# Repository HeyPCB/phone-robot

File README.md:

# Bolt, the phone stand robot

**A little robot that holds your phone, charges it, and peeks over the top to tell you how it's eating.**

Bolt is a matte-black robot phone stand with gold eyes. Two kickstands snap out of its belly and slot through its hips; they become the hands your phone sits on, in landscape, leaning back at 70 degrees. Your charger plugs into its left foot and your phone's cable into its right: a 5 V USB-C pass-through that powers the phone port only when a phone is attached, offers the phone what the charger can give (up to 1.5 A), and measures the charge current. Its two RGB eyes peek over the phone and show it: orange and pulsing while the phone eats, green when it is full.

| Layers | Size | Parts | Nets | Connections routed | Vias | ERC errors | DRC errors / unconnected / parity | BOM @100 |
|---|---|---|---|---|---|---|---|---|
| 2 | 80.1 x 125.4 mm | 31 (+4 pads) | 21 | 76 -> 0 open | 35 | 0 | 0 / 0 / 0 | $1.33 |

**Not fabricated, assembled or powered yet.** Every number on this page is measured by KiCad 10.0.6 on
the files in this repository ([`report.json`](report.json), [`measured.json`](measured.json)) or read
from the live JLC/LCSC catalogue ([`bom_cost.json`](bom_cost.json)).

| | |
|---|---|
| Spec, power budget, BOM | [`SPEC.md`](SPEC.md) |
| Store copy | [`STORE_COPY.md`](STORE_COPY.md) |
| KiCad 10 project | [`kicad/`](kicad/) |
| Gerbers, drill, BOM, CPL, STEP, schematic PDF | [`fab/`](fab/) |
| Firmware | [`firmware/`](firmware/) |
| Renders | [front](media/top.png), [back](media/bottom.png), [hero](media/hero.png), [Circuit World thumbnail](media/circuit-world.png) |
| Brief and generator | [`design/`](design/) |

## What's on it

- **USB-C in:** a 5 V sink with 5.1k Rd; the CH32V003 reads the charger's advertised current on its CC lines.
- **USB-C out:** a 5 V source with GPIO-driven Rp (22k for 1.5 A, 56k for default USB power), an AO3401A switch with soft start that turns on only after the phone's Rd is seen for 150 ms, and a 10k bleeder.
- **Current:** 20 mOhm shunt and INA180A2 (gain 50), 1 V per amp into the ADC; over-current trips the port.
- **Face:** two WS2812C-2020 eyes over the phone; the gold antenna ball is a capacitive touch pad for night mode.
- **Stand:** two snap-out kickstands (four tabs, drilled mouse bites) through 1.85 mm slots; phones up to 12.5 mm thick; no PD, 5 V only (7.5 W).

## Finish

Matte Black solder mask, White silkscreen, ENIG copper finish, 1.6 mm FR4, top-side SMT assembly (J1, J2: an SMD part whose shell legs go through plated holes, soldered on the same SMT line).
The gold art is bare copper under a mask opening (ENIG), drawn with its own keep-out so no track runs
under it. The QR code on the back opens [https://heypcb.ai/world/b/e8b0eb778647](https://heypcb.ai/world/b/e8b0eb778647).

## How it was made

Designed with the HeyPCB method on KiCad 10.0.6, headless, by the `heypcb-kicad` pipeline: a written
brief composed from reusable circuit blocks, every pin from KiCad's own symbol library, every part bound
to an LCSC number from a dated catalogue read, then ERC, a netlist round trip, locked placement,
Freerouting 2.4.1, pours, silkscreen and board art, DRC with schematic parity, DFM and a fab gate,
each stage gated by a measurement. `design/make_brief.py` regenerates the brief (outline, part
locks and art) from code.

Part of the [heypcb.ai merch collection](https://github.com/HeyPCB/merch).

## License

Hardware: [CERN-OHL-S v2](LICENSE). Firmware: MIT (see [`firmware/LICENSE`](firmware/LICENSE)). KiCad's symbol, footprint and 3D
libraries used in the design are CC-BY-SA 4.0 with the KiCad library exception.

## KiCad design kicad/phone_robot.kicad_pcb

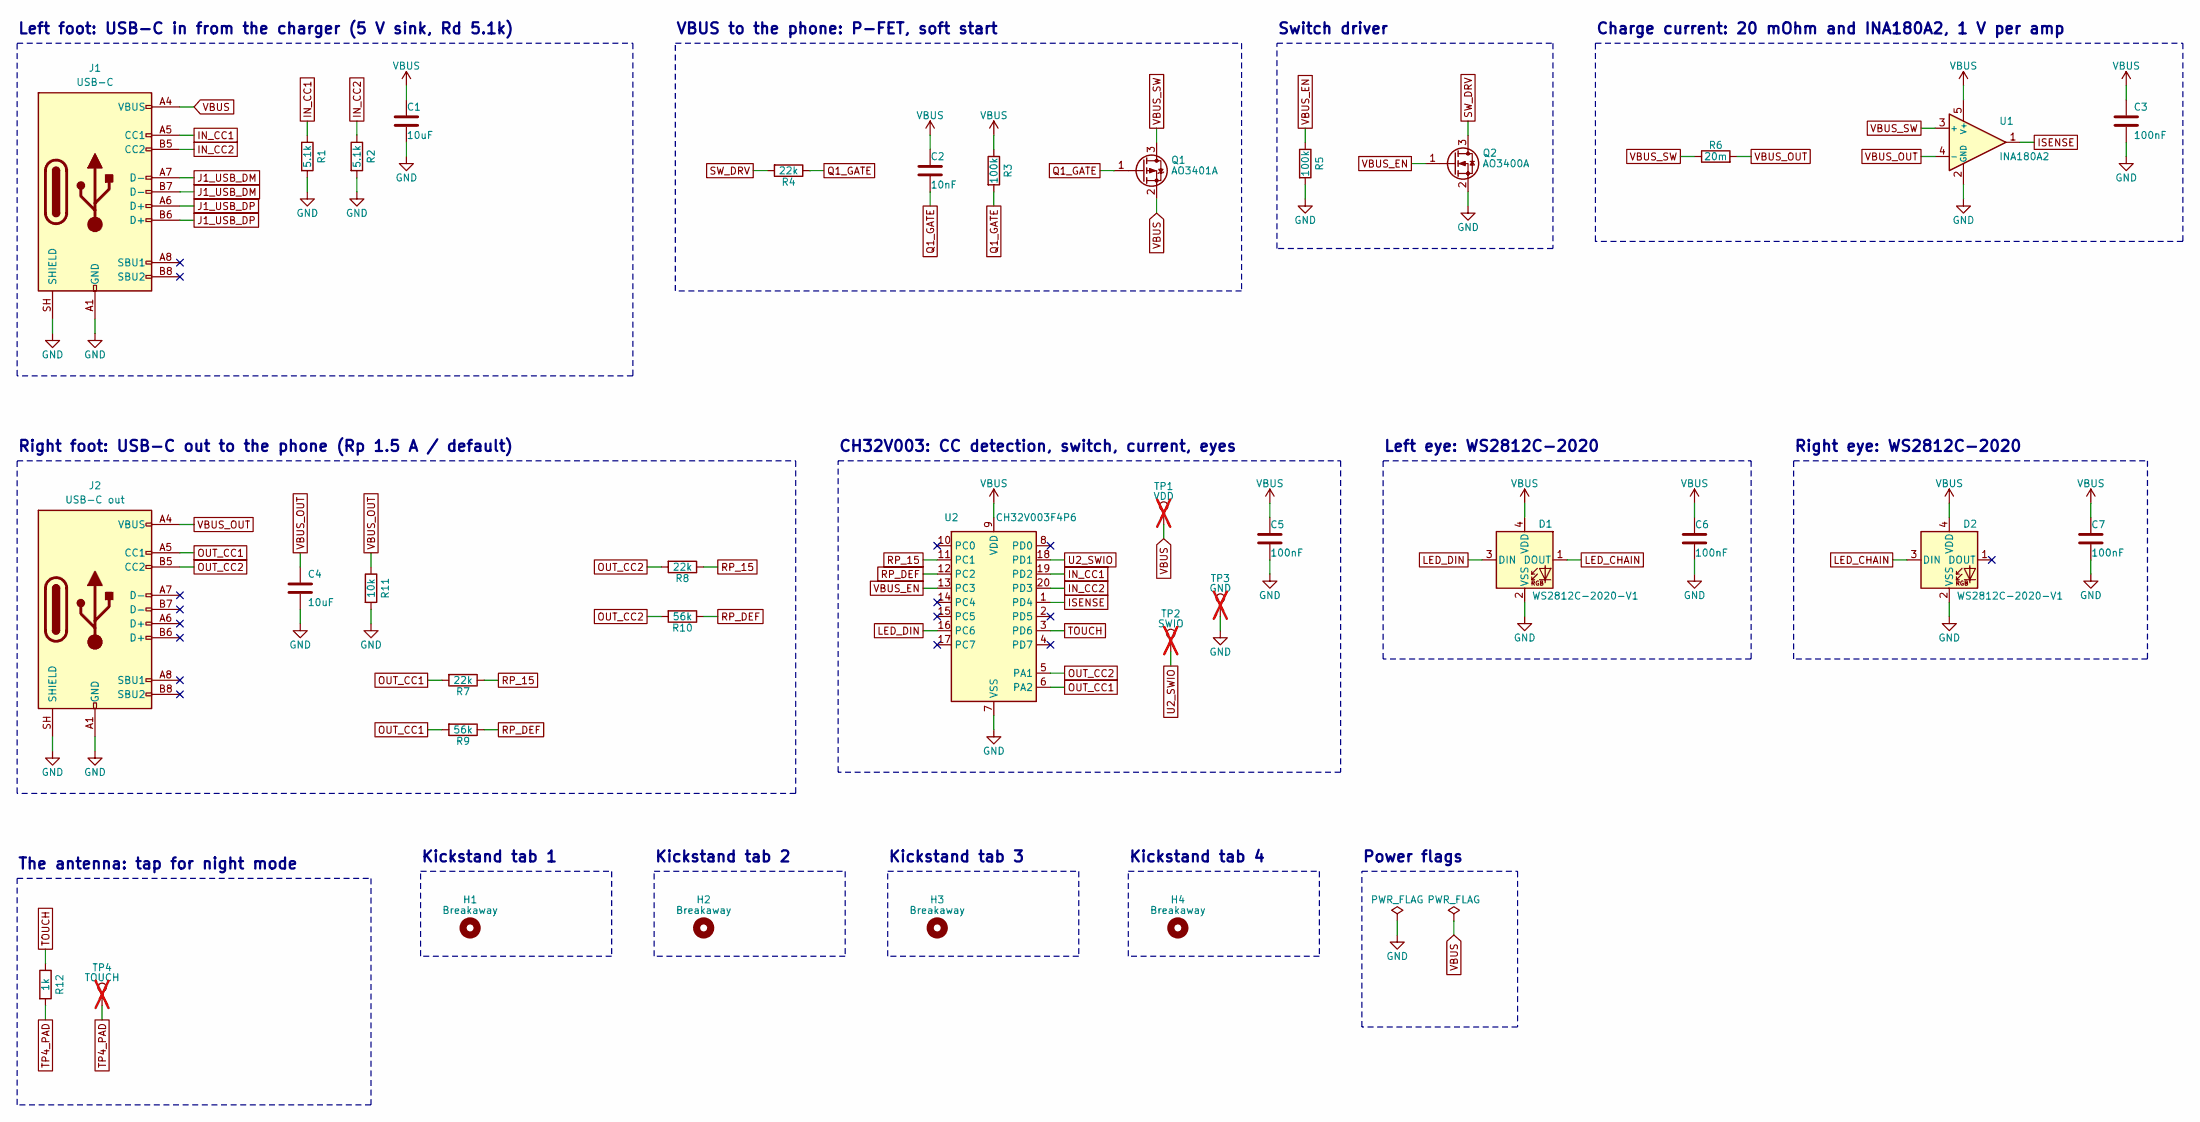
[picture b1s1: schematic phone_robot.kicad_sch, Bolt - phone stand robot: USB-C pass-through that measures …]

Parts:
C1, C4: 10uF; C_0805_2012Metric; MPN CL21A106KAYNNNE; LCSC C15850
C2: 10nF; C_0603_1608Metric; MPN 0603B103K500NT; LCSC C57112
C3, C5: 100nF; C_0603_1608Metric; MPN CC0603KRX7R9BB104; LCSC C14663
C6, C7: 100nF; C_0402_1005Metric; MPN CL05B104KO5NNNC; LCSC C1525
D1, D2: WS2812C-2020-V1; LED_WS2812B-2020_PLCC4_2.0x2.0mm; MPN WS2812C-2020-V1; LCSC C2976072
H1, H2, H3, H4: Breakaway; BreakLine_5h_D0.5mm_P0.85mm
J1: USB-C; USB_C_Receptacle_HRO_TYPE-C-31-M-12; MPN TYPE-C-31-M-12; LCSC C165948
J2: USB-C out; USB_C_Receptacle_HRO_TYPE-C-31-M-12; MPN TYPE-C-31-M-12; LCSC C165948
Q1: AO3401A; SOT-23; MPN AO3401A; LCSC C15127
Q2: AO3400A; SOT-23; MPN AO3400A; LCSC C20917
R1, R2: 5.1k; R_0402_1005Metric; MPN 0402WGF5101TCE; LCSC C25905
R3, R5: 100k; R_0603_1608Metric; MPN 0603WAF1003T5E; LCSC C25803
R4, R7, R8: 22k; R_0603_1608Metric; MPN 0603WAF2202T5E; LCSC C31850
R6: 20m; R_1206_3216Metric; MPN FRM121WFR020TM; LCSC C7420010
R9, R10: 56k; R_0603_1608Metric; MPN 0603WAF5602T5E; LCSC C23206
R11: 10k; R_0402_1005Metric; MPN 0402WGF1002TCE; LCSC C25744
R12: 1k; R_0603_1608Metric; MPN 0603WAF1001T5E; LCSC C21190
TP1: VDD; TestPoint_Pad_1.0x1.0mm; not fitted
TP2: SWIO; TestPoint_Pad_1.0x1.0mm; not fitted
TP3: GND; TestPoint_Pad_1.0x1.0mm; not fitted
TP4: TOUCH; TestPoint_Pad_D4.0mm; not fitted
U1: INA180A2; SOT-23-5; MPN INA180A2IDBVR; LCSC C192764
U2: CH32V003F4P6; TSSOP-20_4.4x6.5mm_P0.65mm; MPN CH32V003F4P6; LCSC C5187096

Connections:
GND: C1.2, C3.2, C4.2, C5.2, C6.2, C7.2, D1.2 (VSS), D2.2 (VSS), J1.A1 (GND), J1.A12 (GND), J1.B1 (GND), J1.B12 (GND), J1.SH (SHIELD), J2.A1 (GND), J2.A12 (GND), J2.B1 (GND), J2.B12 (GND), J2.SH (SHIELD), Q2.2 (S), R1.2, R2.2, R5.2, R11.2, TP3.1, U1.2 (GND), U2.7 (VSS)
IN_CC1: J1.A5 (CC1), R1.1, U2.19 (PD2)
IN_CC2: J1.B5 (CC2), R2.1, U2.20 (PD3)
ISENSE: U1.1, U2.1 (PD4)
J1_USB_DM: J1.A7 (D-), J1.B7 (D-)
J1_USB_DP: J1.A6 (D+), J1.B6 (D+)
LED_CHAIN: D1.1 (DOUT), D2.3 (DIN)
LED_DIN: D1.3 (DIN), U2.16 (PC6)
OUT_CC1: J2.A5 (CC1), R7.2, R9.2, U2.6 (PA2)
OUT_CC2: J2.B5 (CC2), R8.2, R10.2, U2.5 (PA1)
Q1_GATE: C2.2, Q1.1 (G), R3.2, R4.1
RP_15: R7.1, R8.1, U2.11 (PC1)
RP_DEF: R9.1, R10.1, U2.12 (PC2)
SW_DRV: Q2.3 (D), R4.2
TOUCH: R12.1, U2.3 (PD6)
TP4_PAD: R12.2, TP4.1
U2_SWIO: TP2.1, U2.18 (PD1)
VBUS: C1.1, C2.1, C3.1, C5.1, C6.1, C7.1, D1.4 (VDD), D2.4 (VDD), J1.A4 (VBUS), J1.A9 (VBUS), J1.B4 (VBUS), J1.B9 (VBUS), Q1.2 (S), R3.1, TP1.1, U1.5 (V+), U2.9 (VDD)
VBUS_EN: Q2.1 (G), R5.1, U2.13 (PC3)
VBUS_OUT: C4.1, J2.A4 (VBUS), J2.A9 (VBUS), J2.B4 (VBUS), J2.B9 (VBUS), R6.2, R11.1, U1.4 (-)
VBUS_SW: Q1.3 (D), R6.1, U1.3 (+)

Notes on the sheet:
Left foot: USB-C in from the charger (5 V sink, Rd 5.1k)
VBUS to the phone: P-FET, soft start
Switch driver
Charge current: 20 mOhm and INA180A2, 1 V per amp
Right foot: USB-C out to the phone (Rp 1.5 A / default)
CH32V003: CC detection, switch, current, eyes
Left eye: WS2812C-2020
Right eye: WS2812C-2020
The antenna: tap for night mode
Kickstand tab 1
Kickstand tab 2
Kickstand tab 3
Kickstand tab 4
Power flags

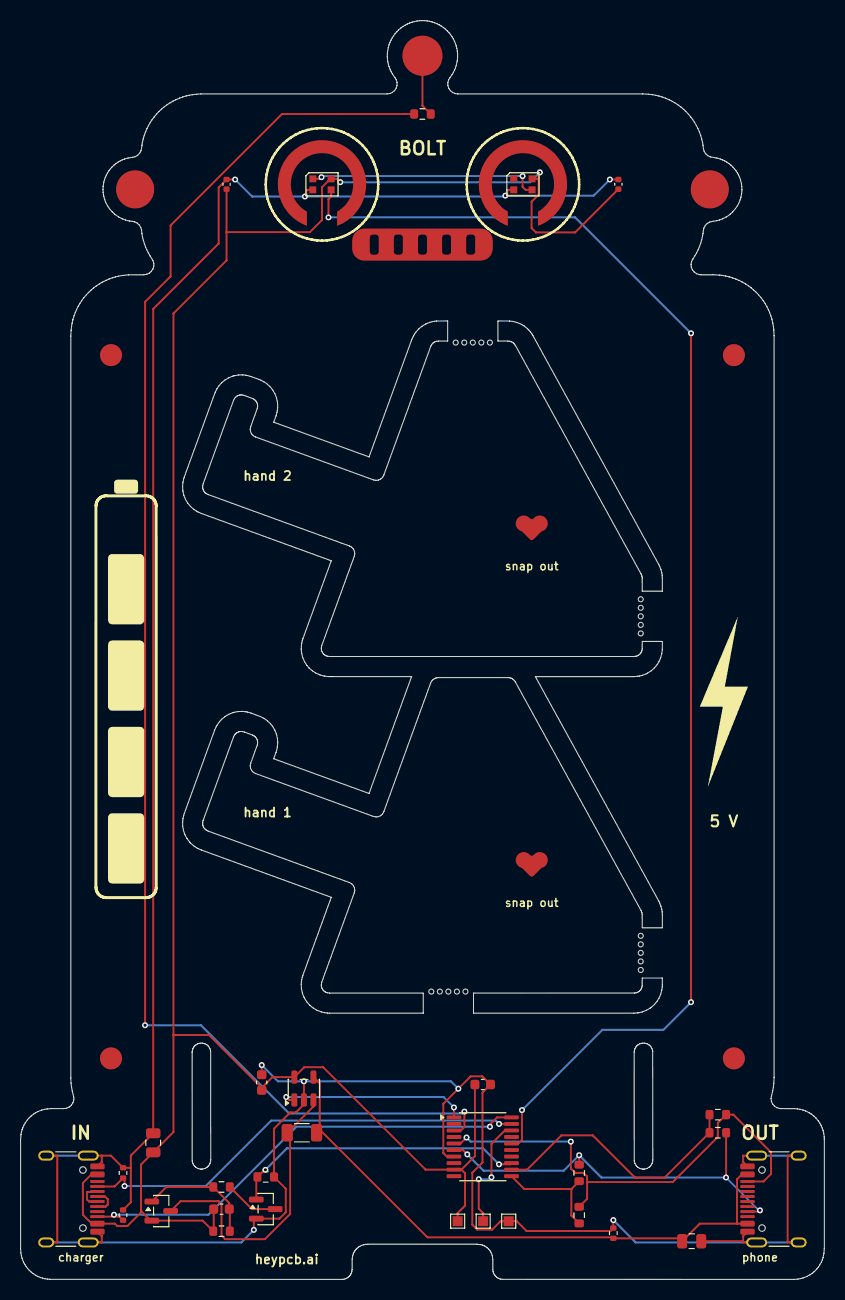
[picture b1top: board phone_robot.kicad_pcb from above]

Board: 2 copper layers, 80.0 x 125.3 mm, 35 parts (0 on the bottom side), 21 nets.

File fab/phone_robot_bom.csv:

"Reference","Value","Footprint","MPN","LCSC","Qty"
"C1,C4","10uF","Capacitor_SMD:C_0805_2012Metric","CL21A106KAYNNNE","C15850","2"
"C2","10nF","Capacitor_SMD:C_0603_1608Metric","0603B103K500NT","C57112","1"
"C3,C5","100nF","Capacitor_SMD:C_0603_1608Metric","CC0603KRX7R9BB104","C14663","2"
"C6,C7","100nF","Capacitor_SMD:C_0402_1005Metric","CL05B104KO5NNNC","C1525","2"
"D1,D2","WS2812C-2020-V1","LED_SMD:LED_WS2812B-2020_PLCC4_2.0x2.0mm","WS2812C-2020-V1","C2976072","2"
"J1","USB-C","Connector_USB:USB_C_Receptacle_HRO_TYPE-C-31-M-12","TYPE-C-31-M-12","C165948","1"
"J2","USB-C out","Connector_USB:USB_C_Receptacle_HRO_TYPE-C-31-M-12","TYPE-C-31-M-12","C165948","1"
"Q1","AO3401A","Package_TO_SOT_SMD:SOT-23","AO3401A","C15127","1"
"Q2","AO3400A","Package_TO_SOT_SMD:SOT-23","AO3400A","C20917","1"
"R1,R2","5.1k","Resistor_SMD:R_0402_1005Metric","0402WGF5101TCE","C25905","2"
"R3,R5","100k","Resistor_SMD:R_0603_1608Metric","0603WAF1003T5E","C25803","2"
"R4,R7,R8","22k","Resistor_SMD:R_0603_1608Metric","0603WAF2202T5E","C31850","3"
"R6","20m","Resistor_SMD:R_1206_3216Metric","FRM121WFR020TM","C7420010","1"
"R9,R10","56k","Resistor_SMD:R_0603_1608Metric","0603WAF5602T5E","C23206","2"
"R11","10k","Resistor_SMD:R_0402_1005Metric","0402WGF1002TCE","C25744","1"
"R12","1k","Resistor_SMD:R_0603_1608Metric","0603WAF1001T5E","C21190","1"
"U1","INA180A2","Package_TO_SOT_SMD:SOT-23-5","INA180A2IDBVR","C192764","1"
"U2","CH32V003F4P6","Package_SO:TSSOP-20_4.4x6.5mm_P0.65mm","CH32V003F4P6","C5187096","1"

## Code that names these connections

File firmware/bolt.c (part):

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 *     mode shows the status for 3 s). A fault still blinks, dimly.
 *
 * Pins (from the board's netlist; KiCad symbol MCU_WCH_RiscV:CH32V003FxPx)
 *   PA2 (pin 6)  OUT_CC1   ADC ch 0      PA1 (pin 5)  OUT_CC2   ADC ch 1
 *   PD2 (pin 19) IN_CC1    ADC ch 3      PD3 (pin 20) IN_CC2    ADC ch 4
 *   PD4 (pin 1)  ISENSE    ADC ch 7      PD6 (pin 3)  TOUCH     ADC ch 6, the antenna through 1k
 *   PC1 (pin 11) RP_15     22k Rp drive  PC2 (pin 12) RP_DEF    56k Rp drive
 *   PC3 (pin 13) VBUS_EN   N-FET gate (high = phone port on)
 *   PC6 (pin 16) LED_DIN   the two WS2812C eyes, left then right
 *   PD1 (pin 18) SWIO      programming
 *
 * The MCU runs from VBUS (5 V nominal). CC readings are ratios of that rail, so they do not care what
 * the charger's voltage is; the current reading assumes 5.0 V and is within the charger's tolerance
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#define WS2812BSIMPLE_IMPLEMENTATION
#include "ws2812b_simple.h"

#define PIN_RP15 PC1
#define PIN_RPDEF PC2
#define PIN_EN PC3
#define PIN_LED PC6

#define CH_OUT_CC1 0
#define CH_OUT_CC2 1
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    funDigitalWrite(PIN_EN, FUN_LOW);
    funPinMode(PIN_EN, GPIO_Speed_10MHz | GPIO_CNF_OUT_PP);
    funPinMode(PIN_LED, GPIO_Speed_10MHz | GPIO_CNF_OUT_PP);
    static const uint8_t analog[] = { PA2, PA1, PD2, PD3, PD4 };
    for (unsigned i = 0; i < sizeof analog; i++)
        funPinMode(analog[i], GPIO_CNF_IN_ANALOG);
    systick_init();
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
